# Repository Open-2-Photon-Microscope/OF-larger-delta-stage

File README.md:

# Substage Sample Manipulator

---
### A substitute for a micromanipulator

Our design is a modification of [Open Flexure's Delta Stage model](https://openflexure.org/projects/deltastage/) combined with a 3-axis controller box. 
The delta stage is a reliable and useful way of manipulating a small sample in X, Y and Z axes without having to move the optics of the microscope, as most current setups do.

Our aim is to use it to replace expensive hardware like [Sutter's MP-285](https://www.sutter.com/MICROMANIPULATION/mp285_frame.html), which costs a lot and effectively has to hold and manipulate the entire microscope in midair.
The setup we detail is applicable to small, low-weight samples. 
    _For larger animals such as mice, we encourage further exploration and experimentation in other projects elsewhere (but we would love know what you find before we delve in to it ourselves!!)._

This part of the project consists of two main pieces:
1. The delta stage itself, to hold and move the sample
1. [The 3-axis controller](https://github.com/Open-2-Photon-Microscope/3-axis-controller/tree/main), which uses rotary encoders to manually adjust the stage position, without the need to interface with a computer (although entirely possible).

We have made modifications to OpenFlexure's original design to allow compatability with a thorlabs cage-based substage light-collection path you can find elsewhere in the Open-2-Photon-Microscope GitHub.
Since we adjusted the scale and a few other things in the design, and since the release paper does not provide data, we have been testing the delta stage's movement, measuring how reliably it makes the same movements in a given direction, and how robust it is to drift over time. These data can be found in the 'Movement Metrics Data' folder.

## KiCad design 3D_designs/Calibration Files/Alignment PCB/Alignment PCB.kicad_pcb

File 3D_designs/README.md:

# 3D Designs

## Optics
 - 3D printable thorlabs-compatible holders for lenses / mirrors

## STL
 - All current stl files for 3D printing:
### Centering:
1. centering card - a flat sheet with a raised hole. Slots over thorlabs cage parts held to Delta Stage. Used in conjucntion with centering top stage.
2. centering top stage - interchangable top stage with a hole for aligning with centering card

### Delta Stage for 2P
- Current working version of the Delta Stage
- large enough to contain thorlabs cage and lens (d=2in)

### Spirit Level
- Essential stage top for attaching a spirit level [url]

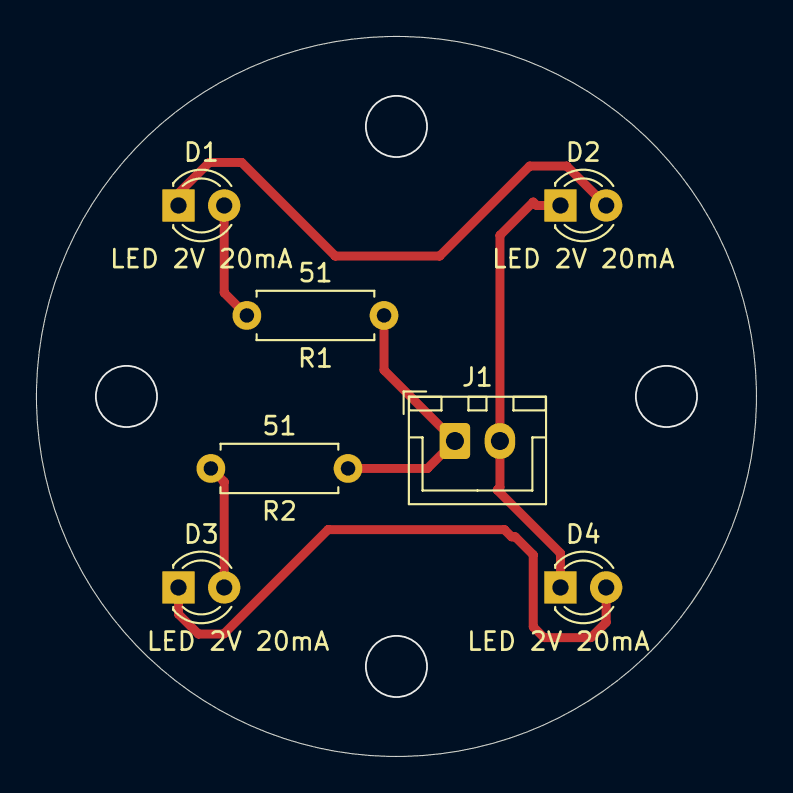
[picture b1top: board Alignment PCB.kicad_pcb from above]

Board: 2 copper layers, 40.0 x 40.0 mm, 7 parts (0 on the bottom side), 6 nets.

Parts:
D1, D2, D3, D4: LED 2V 20mA; LED_D3.0mm
J1: Conn_01x02_Socket; JST_XH_B2B-XH-A_1x02_P2.50mm_Vertical
R1, R2: 51; R_Axial_DIN0207_L6.3mm_D2.5mm_P7.62mm_Horizontal

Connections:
+5V: J1.1, R1.1, R2.1
GND: D2.1 (K), D4.1 (K), J1.2
unnamed: D1.2 (A), R1.2
unnamed: D1.1 (K), D2.2 (A)
unnamed: D3.2 (A), R2.2
unnamed: D3.1 (K), D4.2 (A)

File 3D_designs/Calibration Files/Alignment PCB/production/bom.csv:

Designator,Footprint,Quantity,Value,LCSC Part #
"D1, D2, D3, D4",LED_D3.0mm,4,LED 2V 20mA,
J1,JST_XH_B2B-XH-A_1x02_P2.50mm_Vertical,1,Conn_01x02_Socket,
"R1, R2",R_Axial_DIN0207_L6.3mm_D2.5mm_P7.62mm_Horizontal,2,51,

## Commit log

2021-10-25 clean up and rename 3d designs, plus add licenses on all files
2021-11-30 upload preliminary data
2021-12-07 update analysis code
2021-12-15 initial analysis of the prel. data
2023-01-05 start working on adapter for slide holders
2023-01-23 start start working on the adapter
2023-01-23 remove doc files from openflexure delta stage to decrease repo size
2023-01-24 reorganise repos
2023-01-24 update adapter
2023-01-25 update designs and first holder
2023-01-25 update stage design
2023-01-26 reorganise repo
2023-01-26 clean up build
2023-02-07 update desingsd
2023-04-21 update 3D design
2024-02-08 Added 2 ImageJ macros :
    - 1_Z_project_and_contrast_imageJ_macro.ijm :
    From the raw .tiff files, average the slices and tweak intensity and contrast.
    Outputs the flattened image as a .tiff in a dedicated subfolder "Z_proj" in the same directory as the input files.
    Doesn't process stacks containing the wrong number of slices (filters out faulty recordings).
    - 2_Alignment_and_drift_imageJ_macro.ijm :
    This script select the correct files for alignment according to user input ( All zeros, X displacement, Y displacement or ALL)
2024-02-27 Added python version of XY translation analysis
    Files should be used as follow :
    - 1. Run Z_projection_and_contrast_enhancement.py on raw stack.tiff files (calls functions defined in Z_proj_functions.py). This script averages all slices in the stack, and outputs the projected ima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
    - 2. Run Sort_and_align_skimage_cross_correlation.py on the projected files obtained from 1. (calls functions defined in Registration_cross_correlation.py). This script applies a cross correlation fu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
2024-03-12 Updated delta stage and alignment designs
    + Tidied files.
    + Added updated deltastage scad and stl files.
    + Added alignment scad and stl files.
    + Added README.
2024-04-26 Updated documentation
2024-06-04 Rename code/1_Z_project_and_contrast_imageJ_macro.ijm to code/Old_versions/1_Z_project_and_contrast_imageJ_macro.ijm
2024-06-04 Rename code/2_Alignment_and_drift_imageJ_macro.ijm to code/Old_versions/2_Alignment_and_drift_imageJ_macro.ijm
2024-06-26 updating calibration top
    thinner slits for LEDs and wider holes to fit m3 screws
    general tidying
2024-07-15 Alignment PCB
    Created Alignment PCB
    Moved alignment/calibration STLs to Calibration Files folder
2024-07-25 small updates on aligment pcb, create files for producton
2024-07-25 Added magnets for calibration parts
    delta stage and calibration body now have holes for six 3x2 magnets. Maybe will remove the need for the feet on calibration body soon
2024-07-26 Fixed Delta Stage Bug
    One arm of the deltastage was merged into the body somehow... now fixed
    ofds snap.scad file is a snapshot from before prior update
2024-08-01 Documentation
    Updated documentation
2024-08-12 modified calibration top
    There is a slit in the calibration top to allow the wire to pass from above to below without needing to be passed under the stage
2024-08-13 removed slant holes from calibration
    The alignment for the stage can be done by magnets, no need for extra connectors
2024-08-13 modification to calibration top slit
    stage_calibration.scad module calibration_body now has parameter slit, which can specify thickness.
2024-10-25 Added expanded designs for egg chamber
    compatability with drosophila embryo chambers
2024-10-25 lowered mic slide height
2024-10-25 create petri dish holder
2024-11-04 Create separate scripts for jpeg data
2024-11-04 updating jpeg drifta data handling
    fixes truncation of data by bypassing z_stack removal
2024-11-05 Minor fixes to drift analysis pipeline
    -Fixed cv2.plot() causing multiple fragmented plots rather than one concatenated one.
    -added "m" functionality for jpeg image pipeline to allow more flexible definitions of t1 t2 etc
2024-11-06 Added USB data collection
    -better file naming
    -includes custom minutes
2024-11-12 Adapted for scale + bug fixes
    -Fixed file naming inconsistency in collect_data.py
    -adapted collect_data.py to create multiple folders for consecutive runs
    - fixed(?) webcam not connecting bug by incorporating VideoCapture object as an attribute of Collector
2024-11-12 Added README.md
    -Trimmed some unnecessary code
    -Added documentation for collecting data
2024-11-12 Iterations as user input
2024-11-13 fixing more webcam issues
2024-12-12 Modified feet .scad
    Added slot for attaching endstop microswitch
2025-02-27 Tidied files
2025-03-04 Updated drift data collection
2025-04-16 drift data collection
    Updated to use USB microscope instead of 2P
    Fixes several causes of crashes
2025-05-13 Tweaking analysis scripts
2025-05-27 Fixed S5 line 85
2025-05-28 Plotting and saving data
2025-06-03 Tidying unused files
2025-06-03 Updating analysis pipeline
2025-06-05 Tweaks to analysis
2025-06-12 Added multiple licenses
    Hardware is CERN OHL v1.2
    Software is GNU OHL v3.0
2025-08-28 Data analysis updates
2025-08-28 Movement reliability automation
2025-09-02 Update reliability scripts
